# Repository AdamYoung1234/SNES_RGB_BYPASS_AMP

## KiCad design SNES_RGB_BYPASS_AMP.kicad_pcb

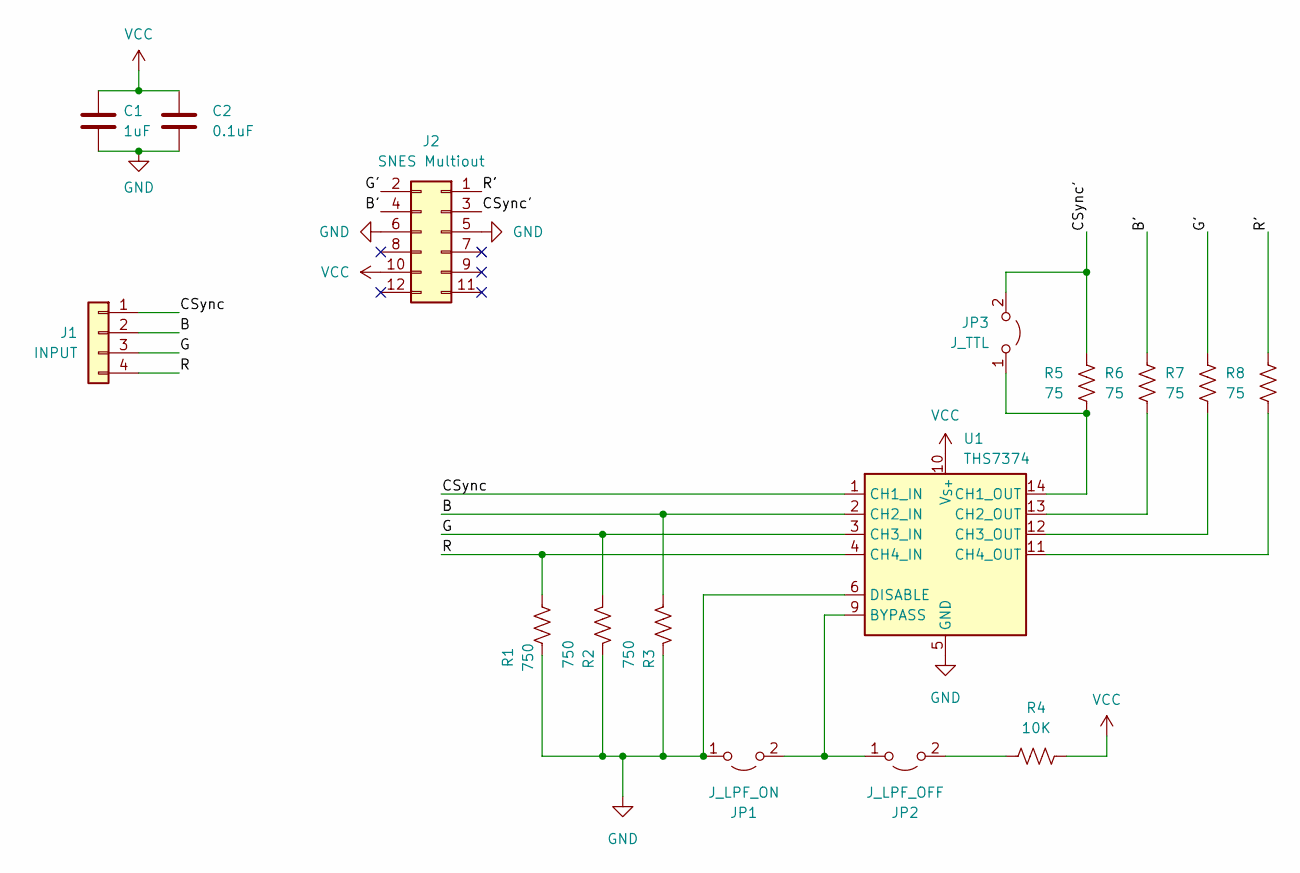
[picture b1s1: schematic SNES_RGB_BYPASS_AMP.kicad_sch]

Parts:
C1: 1uF; C_0805_2012Metric
C2: 0.1uF; C_0805_2012Metric
J1: INPUT; PinHeader_1x04_P2.54mm_Vertical
J2: SNES Multiout; PinHeader_2x06_P2.54mm_Vertical
JP1: J_LPF_ON; SolderJumper-2_P1.3mm_Open_Pad1.0x1.5mm
JP2: J_LPF_OFF; SolderJumper-2_P1.3mm_Open_Pad1.0x1.5mm
JP3: J_TTL; SolderJumper-2_P1.3mm_Open_Pad1.0x1.5mm
R1, R2, R3: 750; C_0805_2012Metric
R4: 10K; C_0805_2012Metric
R5, R6, R7, R8: 75; C_0805_2012Metric
U1: THS7374; TSSOP-14_4.4x5mm_P0.65mm

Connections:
/B: J1.2, R3.2, U1.2 (CH2_IN)
/B': J2.4, R6.1
/CSync: J1.1, U1.1 (CH1_IN)
/CSync': J2.3, JP3.2 (B), R5.1
/G: J1.3, R2.2, U1.3 (CH3_IN)
/G': J2.2, R7.1
/R: J1.4, R1.2, U1.4 (CH4_IN)
/R': J2.1, R8.1
GND: C1.2, C2.2, J2.5, J2.6, JP1.1 (A), R1.1, R2.1, R3.1, U1.5 (GND), U1.6 (DISABLE)
unnamed: JP1.2 (B), JP2.1 (A), U1.9 (BYPASS)
unnamed: JP2.2 (B), R4.1
unnamed: JP3.1 (A), R5.2, U1.14 (CH1_OUT)
unnamed: R6.2, U1.13 (CH2_OUT)
unnamed: R7.2, U1.12 (CH3_OUT)
unnamed: R8.2, U1.11 (CH4_OUT)
VCC: C1.1, C2.1, J2.10, R4.2, U1.10 (V_{S+})

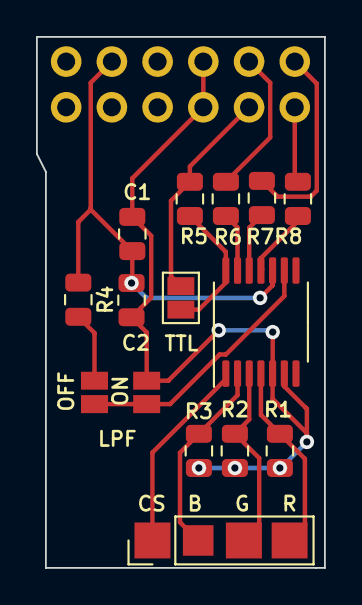
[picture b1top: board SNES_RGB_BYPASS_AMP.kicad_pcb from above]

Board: 2 copper layers, 16.0 x 29.5 mm, 16 parts (1 on the bottom side), 16 nets.

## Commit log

2023-09-01 Update silkscreen
2023-09-03 fix errors
